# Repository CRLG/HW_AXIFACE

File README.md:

# HW_AXIFACE
Carte électronique AXIFACE pour servo-moteurs AX: schéma et routage

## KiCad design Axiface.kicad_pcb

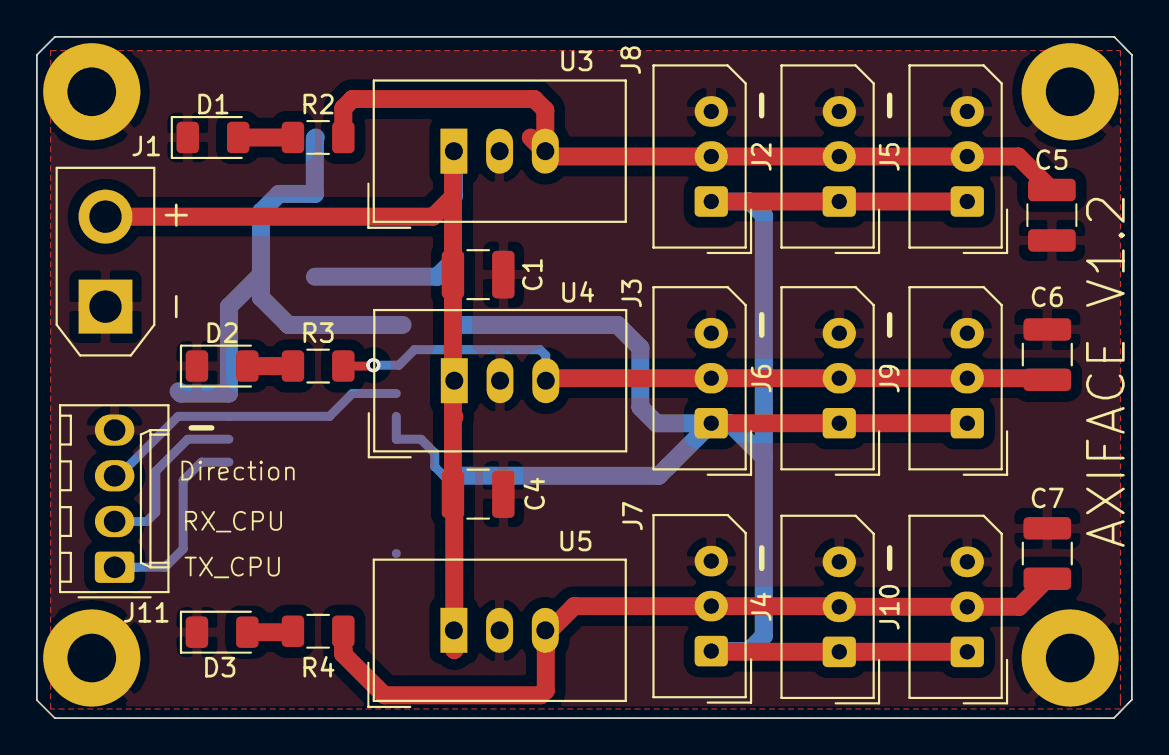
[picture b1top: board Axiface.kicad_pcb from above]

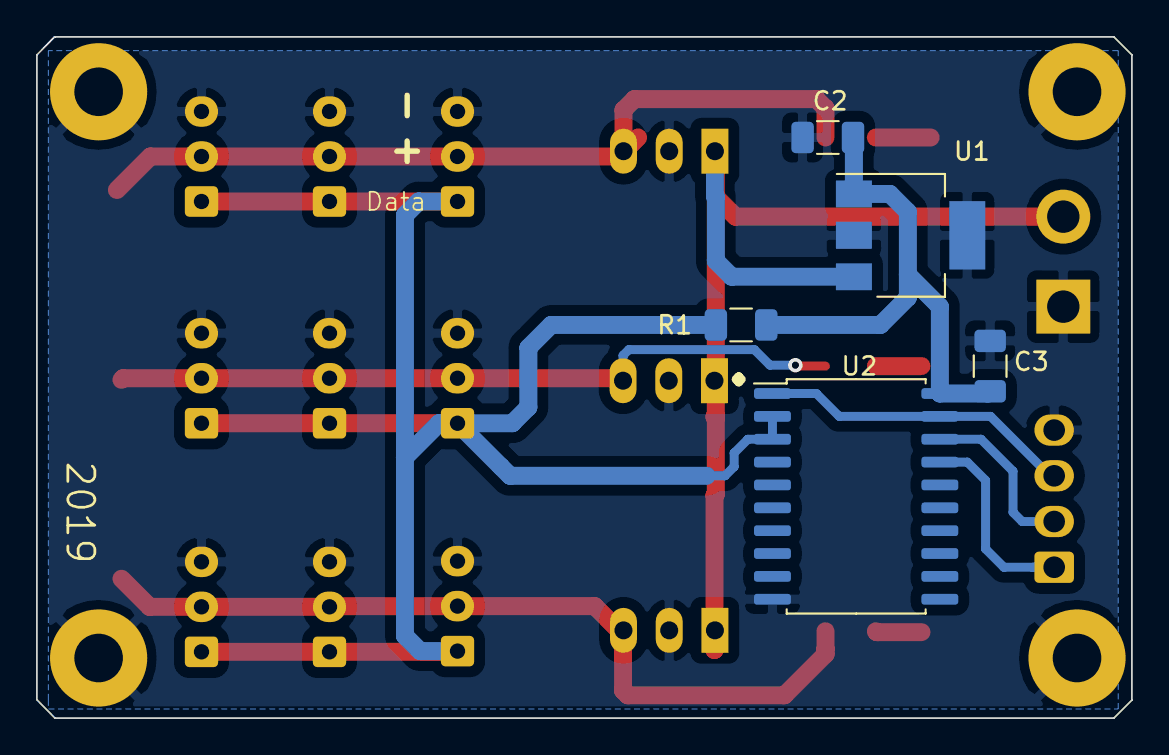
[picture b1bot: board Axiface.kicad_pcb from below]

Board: 2 copper layers, 60.8 x 37.8 mm, 34 parts (5 on the bottom side), 13 nets.

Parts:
C1, C4, C5, C6, C7: 47u; C_1210_3225Metric
C2: 1u; C_1206_3216Metric
C3: 100n; C_1206_3216Metric
D1, D2, D3: LED; LED_1206_3216Metric
H1, H2, H3, H4: MountingHole_Pad; MountingHole_2.7mm_M2.5_Pad
J1: Conn_01x02; AMASS_XT30UPB-F_1x02_P5.0mm_Vertical
J2, J3, J4, J5, J6, J7, J8, J9, J10: Conn_01x03; Molex_SPOX_5267-03A_1x03_P2.50mm_Vertical
J11: Conn_01x04; Molex_KK-254_AE-6410-04A_1x04_P2.54mm_Vertical
R1: 10k; R_1206_3216Metric
R2, R3, R4: 1.8k; R_1206_3216Metric
U1: MCP1804x-5002xDB; SOT-223-3_TabPin2
U2: 74HC241; SOIC-20W_7.5x12.8mm_P1.27mm
U3, U4, U5: TSR_2-2490; Converter_DCDC_TRACO_TSR-2_THT

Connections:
/9V_AX_#1: C5.1, J2.2, J5.2, J8.2, R2.2, U3.3
/9V_AX_#2: C6.1, J3.2, J6.2, J9.2, R3.2, U4.3
/9V_AX_#3: C7.1, J4.2, J7.2, J10.2, R4.2, U5.3
/AxBus: J2.1, J3.1, J4.1, J5.1, J6.1, J7.1, J8.1, J9.1, J10.1, R1.2, U2.2, U2.3
/DIRECTION: J11.3, U2.1, U2.19
/RX_CPU: J11.2, U2.18
/TX_CPU: J11.1, U2.17
/VBAT: C1.1, C4.1, J1.2, U1.3, U3.1, U4.1, U5.1
GND: C1.2, C2.2, C3.1, C4.2, C5.2, C6.2, C7.2, D1.1, D2.1, D3.1, H1.1, H2.1, H3.1, H4.1, J1.1, J2.3, J3.3, J4.3, J5.3, J6.3, J7.3, J8.3, J9.3, J10.3, J11.4, U1.2, U2.10, U3.2, U4.2, U5.2
unnamed: D1.2, R2.1
unnamed: D2.2, R3.1
unnamed: D3.2, R4.1
VCC: C2.1, C3.2, R1.1, U1.1, U2.20

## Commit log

2019-06-23 Ajout de KICAD_LIB comme sous-module du projet
    KICAD_LIB est la librairie de composants et footprints CRLG pour KICAD
2019-06-24 Version en cours Axiface
2019-07-07 Mise à jour schématique + placement composants sur PCB
2019-07-11 Mise à jour du schéma et pcb
2019-07-11 Ajout de la lib convert DCDC au projet
2019-07-17 Mise à jour avant routage
2019-07-17 Mise à jour schéma + routage
2019-07-19 Dernières évolutions mineures avant mise en fabrication
2019-07-30 Correction footprint TRACO TSR_2 + changement ref RS 47uF
    La référence initiale n'est plus distribuée chez RS
    Correction footprint
2019-08-10 Correction erreur d'empreinte sur les Traco 9V
2019-08-25 #1 Correction sérigraphie RX_CPU<->TX_CPU sur la couche supérieure
2020-08-28 Mise à jour KICAD_LIB pour bénéfcier du modèle 3D de la carte en .step
